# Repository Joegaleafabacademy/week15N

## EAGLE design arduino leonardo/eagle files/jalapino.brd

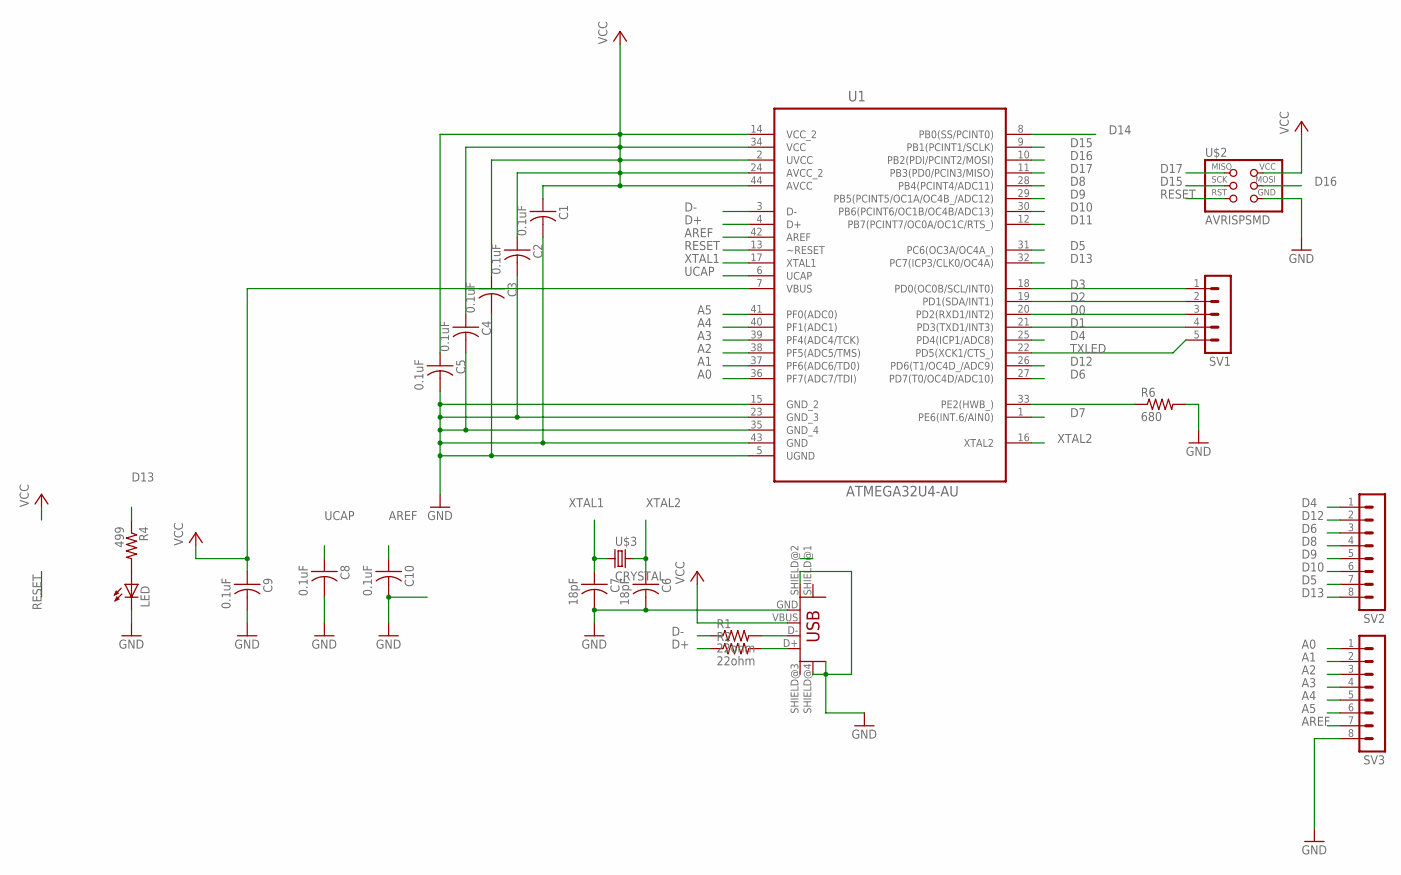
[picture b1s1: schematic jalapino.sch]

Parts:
C1, C2, C3, C4, C5, C8, C9, C10: 0.1uF; C1206FAB
C6, C7: 18pF; C1206FAB
LED: LED1206; 1206
R1, R2: 22ohm; R1206FAB
R4: 499; 1206
R6: 680; R1206FAB
SV1: MA05-1
SV2, SV3: MA08-1
U1: ATMEGA32U4-AU; QFP80P1200X1200X120-44N
U$1: USB_MINIB
U$2: AVRISPSMD; 2X03SMD
U$3: CRYSTAL; 2-SMD-5X3MM

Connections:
A0: SV3.1, U1.36 (PF7(ADC7/TDI))
A1: SV3.2, U1.37 (PF6(ADC6/TD0))
A2: SV3.3, U1.38 (PF5(ADC5/TMS))
A3: SV3.4, U1.39 (PF4(ADC4/TCK))
A4: SV3.5, U1.40 (PF1(ADC1))
A5: SV3.6, U1.41 (PF0(ADC0))
AREF: C10.1, SV3.7, U1.42 (AREF)
D0: SV1.3, U1.20 (PD2(RXD1/INT2))
D1: SV1.4, U1.21 (PD3(TXD1/INT3))
D2: SV1.2, U1.19 (PD1(SDA/INT1))
D3: SV1.1, U1.18 (PD0(OC0B/SCL/INT0))
D4: SV2.1, U1.25 (PD4(ICP1/ADC8))
D5: SV2.7, U1.31 (PC6(OC3A/OC4A_))
D6: SV2.3, U1.27 (PD7(T0/OC4D/ADC10))
D7: U1.1 (PE6(INT.6/AIN0))
D8: SV2.4, U1.28 (PB4(PCINT4/ADC11))
D9: SV2.5, U1.29 (PB5(PCINT5/OC1A/OC4B_/ADC12))
D10: SV2.6, U1.30 (PB6(PCINT6/OC1B/OC4B/ADC13))
D11: U1.12 (PB7(PCINT7/OC0A/OC1C/RTS_))
D12: SV2.2, U1.26 (PD6(T1/OC4D_/ADC9))
D13: R4.1, SV2.8, U1.32 (PC7(ICP3/CLK0/OC4A))
D14: U1.8 (PB0(SS/PCINT0))
D15: U1.9 (PB1(PCINT1/SCLK)), U$2.3 (SCK)
D16: U1.10 (PB2(PDI/PCINT2/MOSI)), U$2.4 (MOSI)
D17: U1.11 (PB3(PD0/PCIN3/MISO)), U$2.1 (MISO)
D+: R2.1, U1.4 (D+)
D-: R1.1, U1.3 (D-)
GND: C1.2, C2.2, C3.2, C4.2, C5.2, C6.2, C7.2, C8.2, C9.2, C10.2, LED.2 (C), R6.2, SV3.8, U1.5 (UGND), U1.15 (GND_2), U1.23 (GND_3), U1.35 (GND_4), U1.43 (GND), U$1.GND, U$1.SHIELD@2 (SHIELD1), U$1.SHIELD@4 (SHIELD3), U$2.6 (GND)
unnamed: R1.2, U$1.D-
unnamed: R2.2, U$1.D+
unnamed: LED.1 (A), R4.2
unnamed: R6.1, U1.33 (PE2(HWB_))
RESET: U1.13 (~RESET), U$2.5 (RST)
TXLED: SV1.5, U1.22 (PD5(XCK1/CTS_))
UCAP: C8.1, U1.6 (UCAP)
VCC: C1.1, C2.1, C3.1, C4.1, C5.1, C9.1, U1.2 (UVCC), U1.7 (VBUS), U1.14 (VCC_2), U1.24 (AVCC_2), U1.34 (VCC), U1.44 (AVCC), U$1.VBUS, U$2.2 (VCC)
XTAL1: C7.1, U1.17 (XTAL1), U$3.P$1 (1)
XTAL2: C6.1, U1.16 (XTAL2), U$3.P$2 (2)

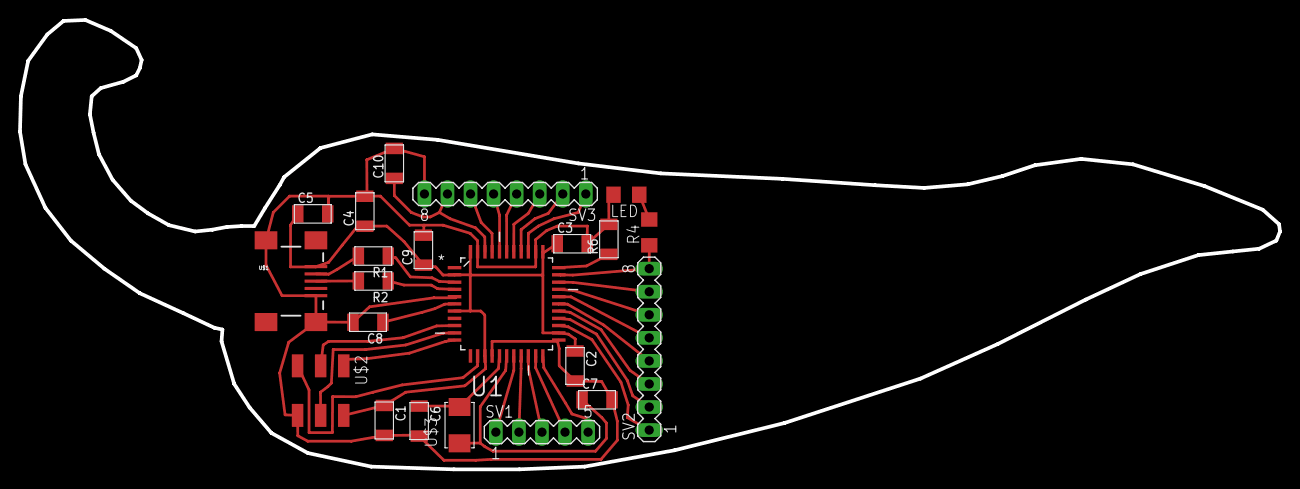
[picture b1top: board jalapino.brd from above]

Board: 2 copper layers, 138.8 x 49.5 mm, 22 parts (0 on the bottom side), 35 nets.
